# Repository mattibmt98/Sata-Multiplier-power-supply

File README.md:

# 5-Bay SATA Drive Power Supply

A 5-channel 12V/5V power board for a SATA port-multiplier drive cage, with
**passive analog staggered spin-up** so five drives never draw their inrush at
the same moment.

**Two 12V DC bricks in** (one barrel jack for bays 1–3, one for bays 4–5), five
12V+5V outputs out. No MCU, no hot-swap: each half powers up and down as a unit.

| | |
|---|---|
| Status | Schematic complete and verified · PCB routed, JLCPCB 2-layer rules |
| Board | 64.9 × 78.8 mm, single-sided placement, 118 parts |
| ERC / DRC | 0 errors, 0 unconnected, 0 schematic-parity issues (93 `connection_width` warnings, 86 of them inherited from v3) |
| BOM | `kicad/digikey_bom.csv`, fully sourced |
| Tool | KiCad 9 — open `kicad/sata_psu.kicad_pro` |

Tag [`v1.0`](../../releases/tag/v1.0) is the earlier single-buck board: 56 parts,
64.2 × 53.3 mm, same switch topology.

## What it does

- **Input, ×2:** barrel jack → 8A cartridge fuse → PMOS reverse-polarity guard →
  1000µF bulk, with a 12V indicator LED tapped *after* the guard so it also
  proves the guard is conducting. `J8` feeds `12V_A` (bays 1–3), `J9` feeds
  `12V_B` (bays 4–5). See "Two inputs" below.
- **Per channel (×5):** high-side P-channel MOSFET on the 12V feed, gate driven
  by an RC network so each channel turns on ~1.5–2s after the previous one and
  ramps softly instead of slamming in; 8.2V zener gate clamp; PPTC polyfuse;
  local bulk + HF decoupling; 4-pin header (12V / GND / GND / 5V) out to a SATA
  pigtail; a 5V indicator LED at the connector.
- **No 3.3V pin anywhere**, by construction — this sidesteps the SATA PWDIS
  failure mode entirely.

## Two inputs, two separate 12V rails

A fully populated cage pulls more than one PJ-063AH should carry — the jack is
an 8A contact and the single-input board fused it at 10A. So the load is
**split**, not paralleled:

```
J8 -> F8 -> Q8 -> 12V_A -> bays 1, 2, 3     worst case ~4.4A
J9 -> F9 -> Q9 -> 12V_B -> bays 4, 5        worst case ~3.4A
```

- The two rails are **never joined**; only ground is common. Two bricks in
  parallel do not share current, and an unplugged one would be back-fed.
- A 5–6A brick per jack is enough. Each half runs on its own: with only `J8`
  plugged, bays 1–3 work and 4–5 are simply off.
- With one to three drives, use bays 1–3 and a single brick on `J8`.
- The split follows the default 5V grouping (U2 → 1–3, U4 → 4–5). A 5V group
  that straddled the two inputs would feed 5V to a drive whose 12V is
  unplugged, so `verify.py` check 5 now refuses it (`DOMAINS` in `gen_sch.py`).

## The 5V rail is configurable, not fixed

Every port has its own local 5V node and its own buck footprint. Adjacent nodes
are joined by 0Ω links. **How a port gets its 5V is a populate choice, not a
layout one** — there is no board variant either way:

```
        U1        U2        U3        U4        U5      <- buck sites
       5V_1 -R61- 5V_2 -R62- 5V_3 -R63- 5V_4 -R64- 5V_5
```

Two tuples at the top of `gen_sch.py` are the whole configuration:

```python
# port:    1      2      3      4      5
BUCKS = (False, True,  False, True,  False)
LINKS = (True,  True,  False, True)        # R61..R64, between port n and n+1
```

The default is the economy build — U2 feeds ports 1–3, U4 feeds 4–5. All-True
`BUCKS` with all-False `LINKS` gives one independent buck per port.

**`R63` open is not decoration.** Fitting it with both U2 and U4 populated
parallels two regulators, and two bucks with slightly different setpoints do not
share load — the higher one takes everything and goes into current limit. That
build draws fine, exports a valid netlist and passes ERC, so `verify.py` check 5
is the only thing that catches it.

This is also what fixed v1's largest problem: one 3A TPS563200 was under-rated
against a five-bay 5V rail. Capping a buck at three ports makes its worst case
2.1A, and the same part is correctly sized.

## The schematic is generated, not drawn

Every coordinate, value and part number lives in Python. Do not hand-edit
the `.kicad_sch` sheets under `kicad/` — they are overwritten.

```bash
py sata_psu.py     # independent SKiDL reference netlist
py gen_sch.py      # build symbols + draw all 7 sheets
py verify.py       # the five checks below
```

**Do not run `gen_pcb.py` any more.** It produces an *unrouted* placement and
predates the routed board; `kicad/sata_psu.kicad_pcb` is now edited in KiCad
(or with pcbnew scripts) and is the source of truth for the layout.

`verify.py` cross-checks the drawn schematic against a *separately written*
SKiDL description of the same circuit, so a wire that only looks like it lands
on a pin gets caught. It runs five checks — ERC, symbol overlap, netlist
equivalence, symbol-pin-vs-pad, and the rail populate rules — each of which
exists because it catches something the others cannot see.

Details, and a list of KiCad file-format gotchas that cost real debugging time,
are in [HANDOFF.md](HANDOFF.md).

## Documents

- [`5bay_sata_psu_project.md`](5bay_sata_psu_project.md) — design intent: why
  staggered sequencing, power budget, block diagram, test plan.
- [`HANDOFF.md`](HANDOFF.md) — implementation: build pipeline, design decisions,
  placement rationale, BOM, and what changed in v2.

## Known open issues

1. Ceramic DC-bias derating will shorten the stagger versus the design table —
   the timing caps want bench tuning, or C0G/film for repeatability.
2. Linear-region SOA during the RC ramp is unverified against the real inrush.
3. The two inputs are staggered independently: bay 1 (domain A) and bay 4
   (domain B) each start their own RC ramp when their own brick is plugged in.
4. The 8A fuse cartridge's DigiKey number (`F2396-ND`) came from a web search
   of the listing, not from the cart — confirm it when ordering.

## Note on `libs/digikey/`

The vendored DigiKey KiCad library is not tracked here (12 MB, and unused — the
regulators moved to KiCad's own `Package_TO_SOT_SMD:SOT-23-6`).
`kicad/fp-lib-table` still carries the entry, so KiCad may warn about a missing
library on first open; either ignore it, drop the row, or restore the clone:

```bash
git clone --depth 1 https://github.com/Digi-Key/digikey-kicad-library libs/digikey
```

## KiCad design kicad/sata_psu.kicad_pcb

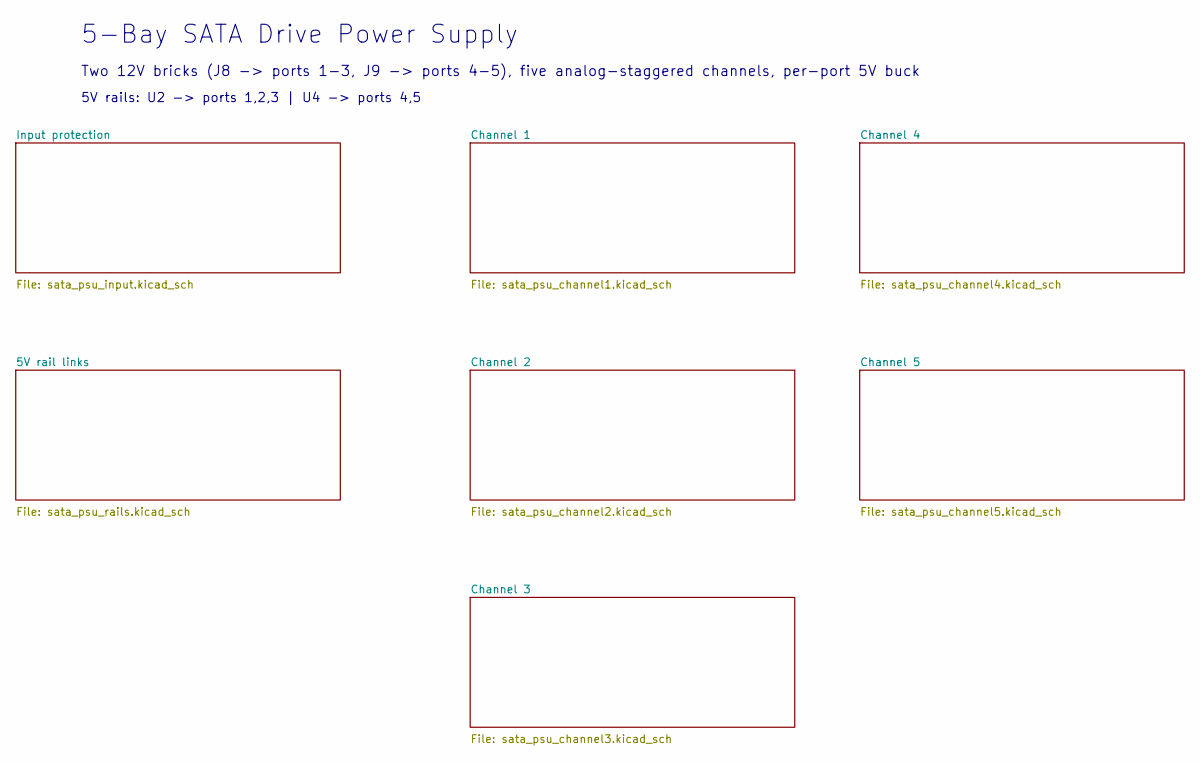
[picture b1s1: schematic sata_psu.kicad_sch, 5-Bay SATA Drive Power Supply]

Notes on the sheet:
5-Bay SATA Drive Power Supply
Two 12V bricks (J8 -> ports 1-3, J9 -> ports 4-5), five analog-staggered channels, per-port 5V buck
5V rails: U2 -> ports 1,2,3 | U4 -> ports 4,5

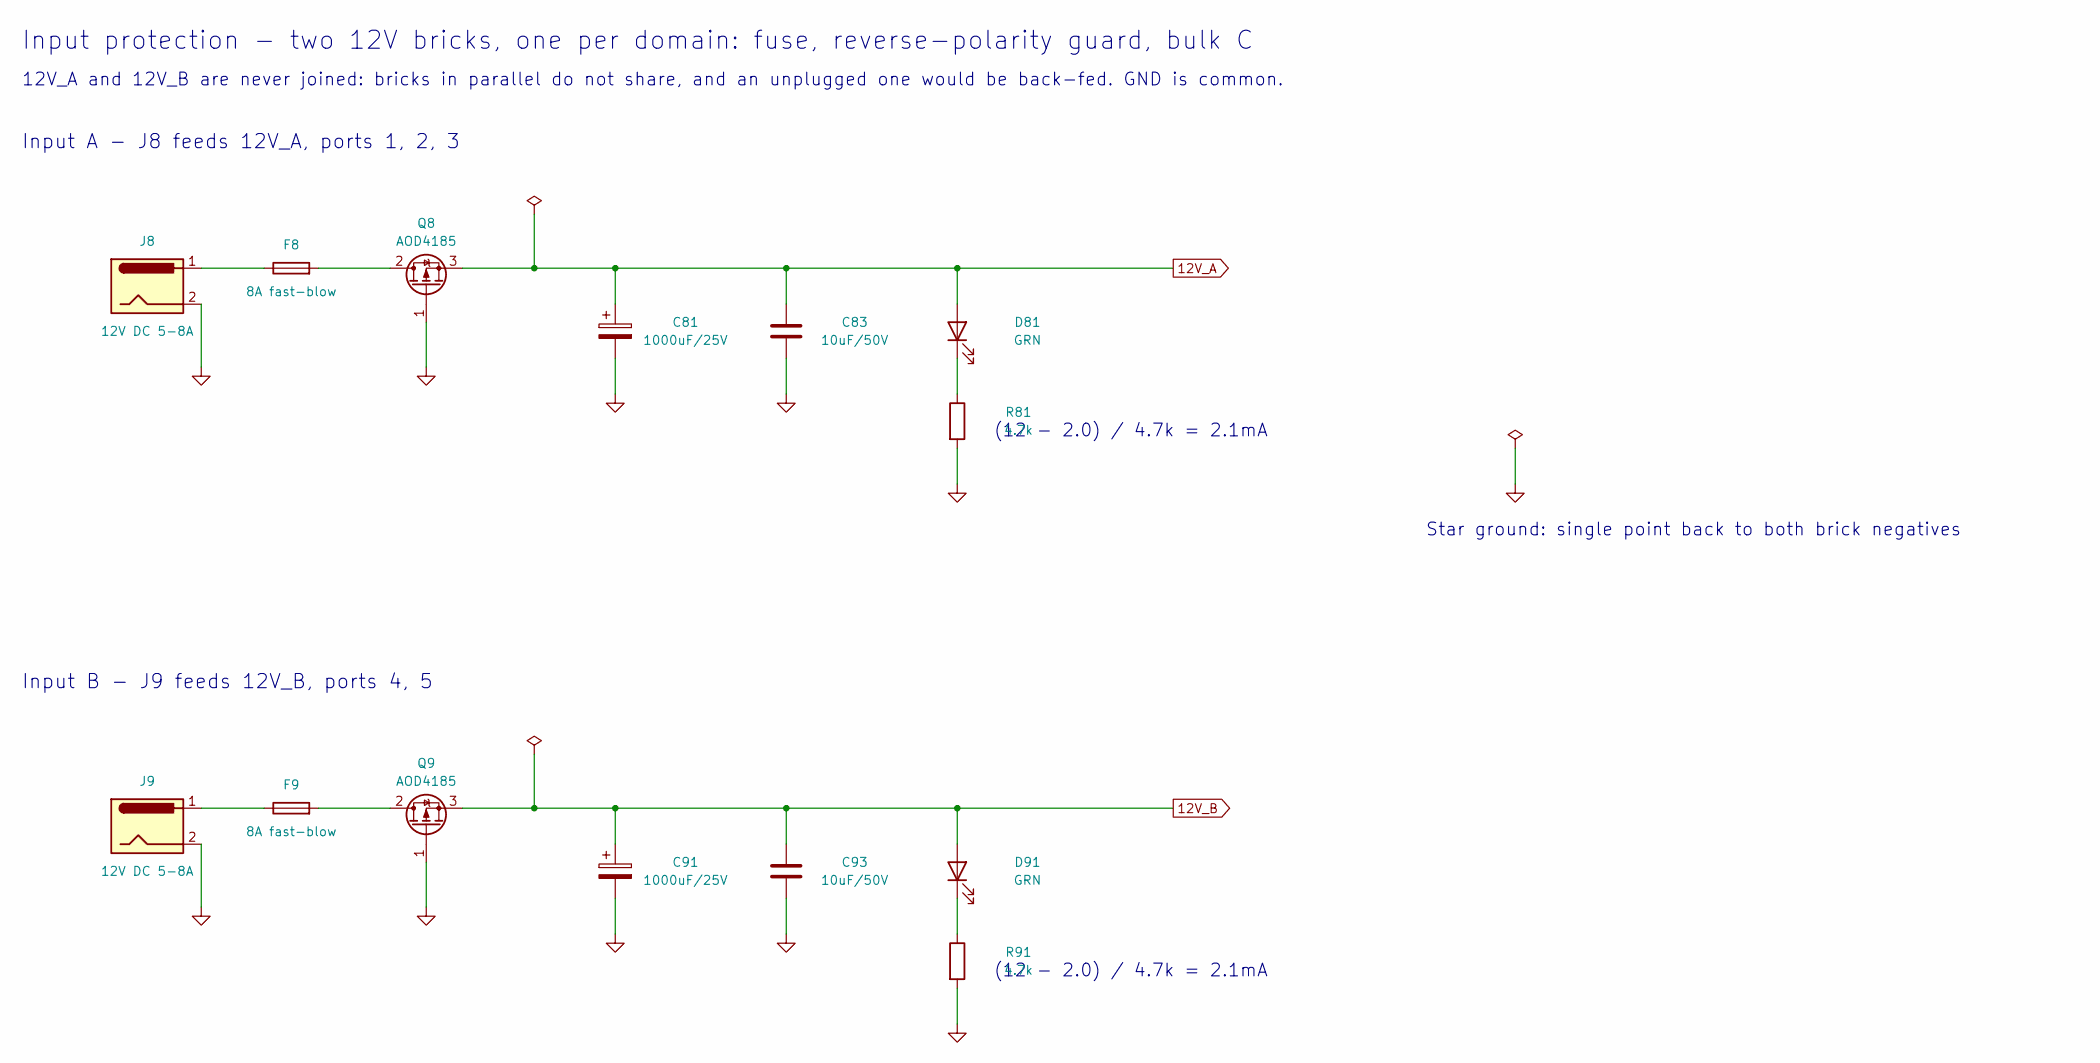
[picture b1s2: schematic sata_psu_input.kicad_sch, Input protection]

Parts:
C81, C91: 1000uF/25V; CP_Radial_D10.0mm_P5.00mm; MPN UVR1E102MPD; DigiKey 493-1065-ND
C83, C93: 10uF/50V; C_1206_3216Metric; MPN CL31A106KBHNNNE; DigiKey 1276-2876-1-ND
D81, D91: GRN; LED_0603_1608Metric
F8, F9: 8A fast-blow; Fuseholder_Clip-5x20mm_Bel_FC-203-22_Lateral_P17.80x5.00mm_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; MPN FC-203-22; DigiKey 507-1703-ND
J8, J9: 12V DC 5-8A; BarrelJack_CUI_PJ-063AH_Horizontal; MPN PJ-063AH; DigiKey CP-063AH-ND
Q8, Q9: AOD4185; TO-252-3_TabPin2; MPN AOD4185; DigiKey 785-1222-2-ND
R81, R91: 4.7k; R_0603_1608Metric

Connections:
12V_A: C81.1, C83.1, D81.2 (A), Q8.3 (S); also elsewhere on the board
12V_B: C91.1, C93.1, D91.2 (A), Q9.3 (S); also elsewhere on the board
GND: C81.2, C83.2, C91.2, C93.2, J8.2, J9.2, Q8.1 (G), Q9.1 (G), R81.2, R91.2; also elsewhere on the board
unnamed: D81.1 (K), R81.1
unnamed: D91.1 (K), R91.1
unnamed: F8.1, J8.1
unnamed: F9.1, J9.1
unnamed: F8.2, Q8.2 (D)
unnamed: F9.2, Q9.2 (D)

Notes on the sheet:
Input protection - two 12V bricks, one per domain: fuse, reverse-polarity guard, bulk C
12V_A and 12V_B are never joined: bricks in parallel do not share, and an unplugged one would be back-fed. GND is common.
Input A - J8 feeds 12V_A, ports 1, 2, 3
(12 - 2.0) / 4.7k = 2.1mA
Input B - J9 feeds 12V_B, ports 4, 5
Star ground: single point back to both brick negatives

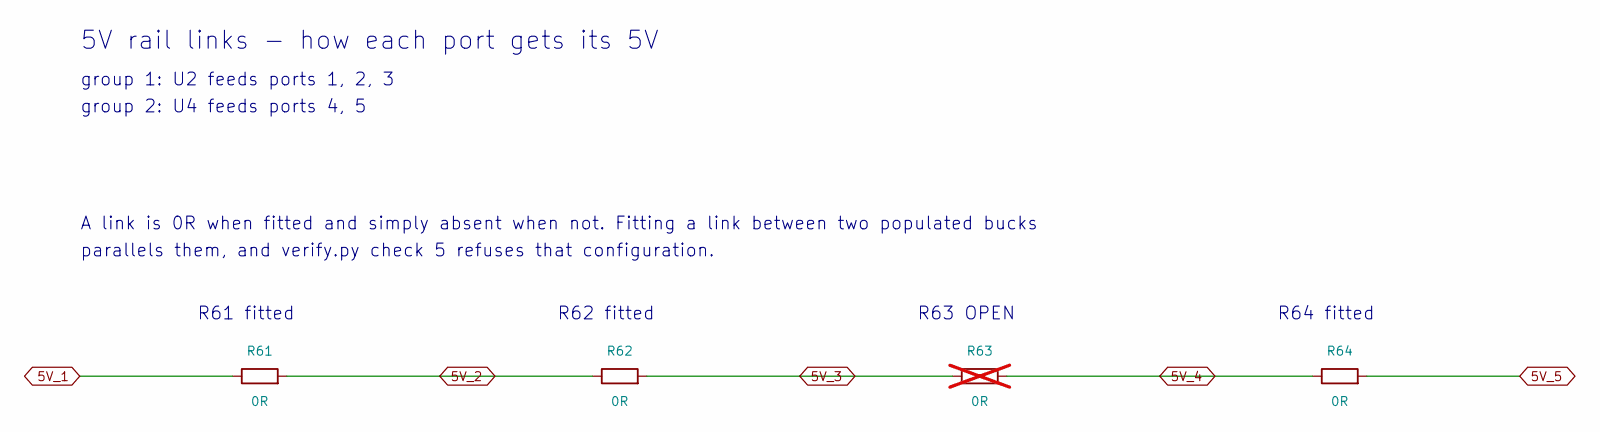
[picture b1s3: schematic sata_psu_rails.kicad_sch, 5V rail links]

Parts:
R61, R62, R64: 0R; R_1206_3216Metric
R63: 0R; R_1206_3216Metric; not fitted

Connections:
5V_1: R61.1; also elsewhere on the board
5V_2: R61.2, R62.1; also elsewhere on the board
5V_3: R62.2, R63.1; also elsewhere on the board
5V_4: R63.2, R64.1; also elsewhere on the board
5V_5: R64.2; also elsewhere on the board

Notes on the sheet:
5V rail links - how each port gets its 5V
group 1: U2 feeds ports 1, 2, 3
group 2: U4 feeds ports 4, 5
A link is 0R when fitted and simply absent when not. Fitting a link between two populated bucks
parallels them, and verify.py check 5 refuses that configuration.
R61 fitted
R62 fitted
R63 OPEN
R64 fitted

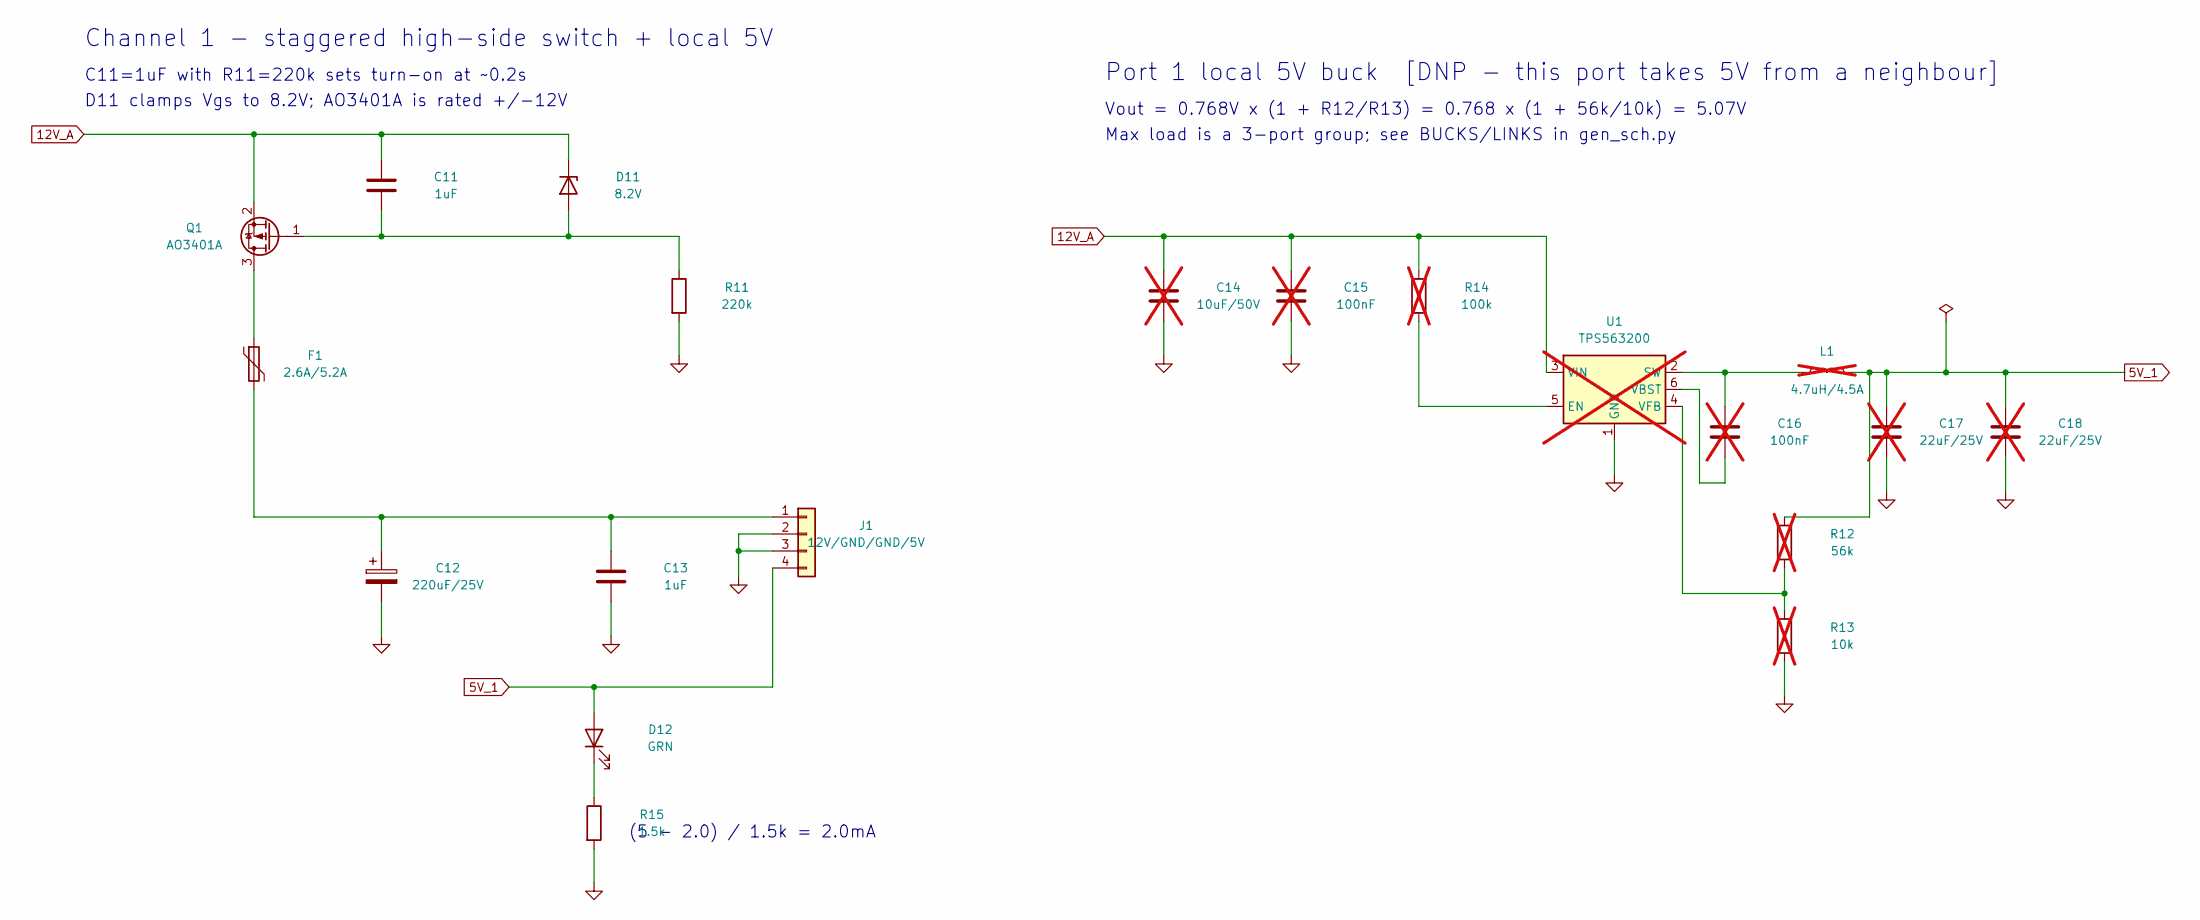
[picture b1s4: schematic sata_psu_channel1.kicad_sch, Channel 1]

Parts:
C11, C13: 1uF; C_0603_1608Metric; MPN CL10A105KB8NNNC; DigiKey 1276-1860-1-ND
C12: 220uF/25V; CP_Radial_D8.0mm_P3.50mm; MPN UVZ1E221MPD; DigiKey 493-1302-ND
C14: 10uF/50V; C_1206_3216Metric; MPN CL31A106KBHNNNE; DigiKey 1276-2876-1-ND; not fitted
C15, C16: 100nF; C_0603_1608Metric; MPN CL10B104KB8NNNC; DigiKey 1276-1000-1-ND; not fitted
C17, C18: 22uF/25V; C_1206_3216Metric; MPN CL31A226KAHNNNE; DigiKey 1276-3047-1-ND; not fitted
D11: 8.2V; D_SOD-123; MPN MMSZ5237B-7-F; DigiKey MMSZ5237B-FDICT-ND
D12: GRN; LED_0603_1608Metric
F1: 2.6A/5.2A; Fuse_1812_4532Metric; MPN 1812L260/16MR; DigiKey F10827CT-ND
J1: 12V/GND/GND/5V; PinHeader_1x04_P2.54mm_Vertical; MPN PRPC004SAAN-RC; DigiKey S1011EC-04-ND
L1: 4.7uH/4.5A; L_Bourns_SRN6045TA; MPN SRN6045TA-4R7M; DigiKey SRN6045TA-4R7MTR-ND; not fitted
Q1: AO3401A; SOT-23; MPN AO3401A; DigiKey 785-1001-1-ND
R11: 220k; R_0603_1608Metric; MPN RC0603FR-07220KL; DigiKey 311-220KHRCT-ND
R12: 56k; R_0603_1608Metric; MPN RC0603FR-0756KL; DigiKey 311-56KHRCT-ND; not fitted
R13: 10k; R_0603_1608Metric; MPN RC0603FR-0710KL; DigiKey 311-10.0KHRCT-ND; not fitted
R14: 100k; R_0603_1608Metric; MPN RC0603FR-07100KL; DigiKey 311-100KHRCT-ND; not fitted
R15: 1.5k; R_0603_1608Metric
U1: TPS563200; SOT-23-6; MPN TPS563200DDCR; DigiKey 296-43663-1-ND; not fitted

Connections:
5V_1: C17.1, C18.1, D12.2 (A), J1.4, L1.2, R12.1; also elsewhere on the board
12V_A: C11.1, C14.1, C15.1, D11.1 (K), Q1.2 (S), R14.1, U1.3 (VIN); also elsewhere on the board
GND: C12.2, C13.2, C14.2, C15.2, C17.2, C18.2, J1.2, J1.3, R11.2, R13.2, R15.2, U1.1 (GND); also elsewhere on the board
unnamed: C11.2, D11.2 (A), Q1.1 (G), R11.1
unnamed: D12.1 (K), R15.1
unnamed: C12.1, C13.1, F1.2, J1.1
unnamed: F1.1, Q1.3 (D)
unnamed: R14.2, U1.5 (EN)
unnamed: C16.1, L1.1, U1.2 (SW)
unnamed: C16.2, U1.6 (VBST)
unnamed: R12.2, R13.1, U1.4 (VFB)

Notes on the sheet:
Channel 1 - staggered high-side switch + local 5V
C11=1uF with R11=220k sets turn-on at ~0.2s
D11 clamps Vgs to 8.2V; AO3401A is rated +/-12V
(5 - 2.0) / 1.5k = 2.0mA
Port 1 local 5V buck [DNP - this port takes 5V from a neighbour]
Vout = 0.768V x (1 + R12/R13) = 0.768 x (1 + 56k/10k) = 5.07V
Max load is a 3-port group; see BUCKS/LINKS in gen_sch.py

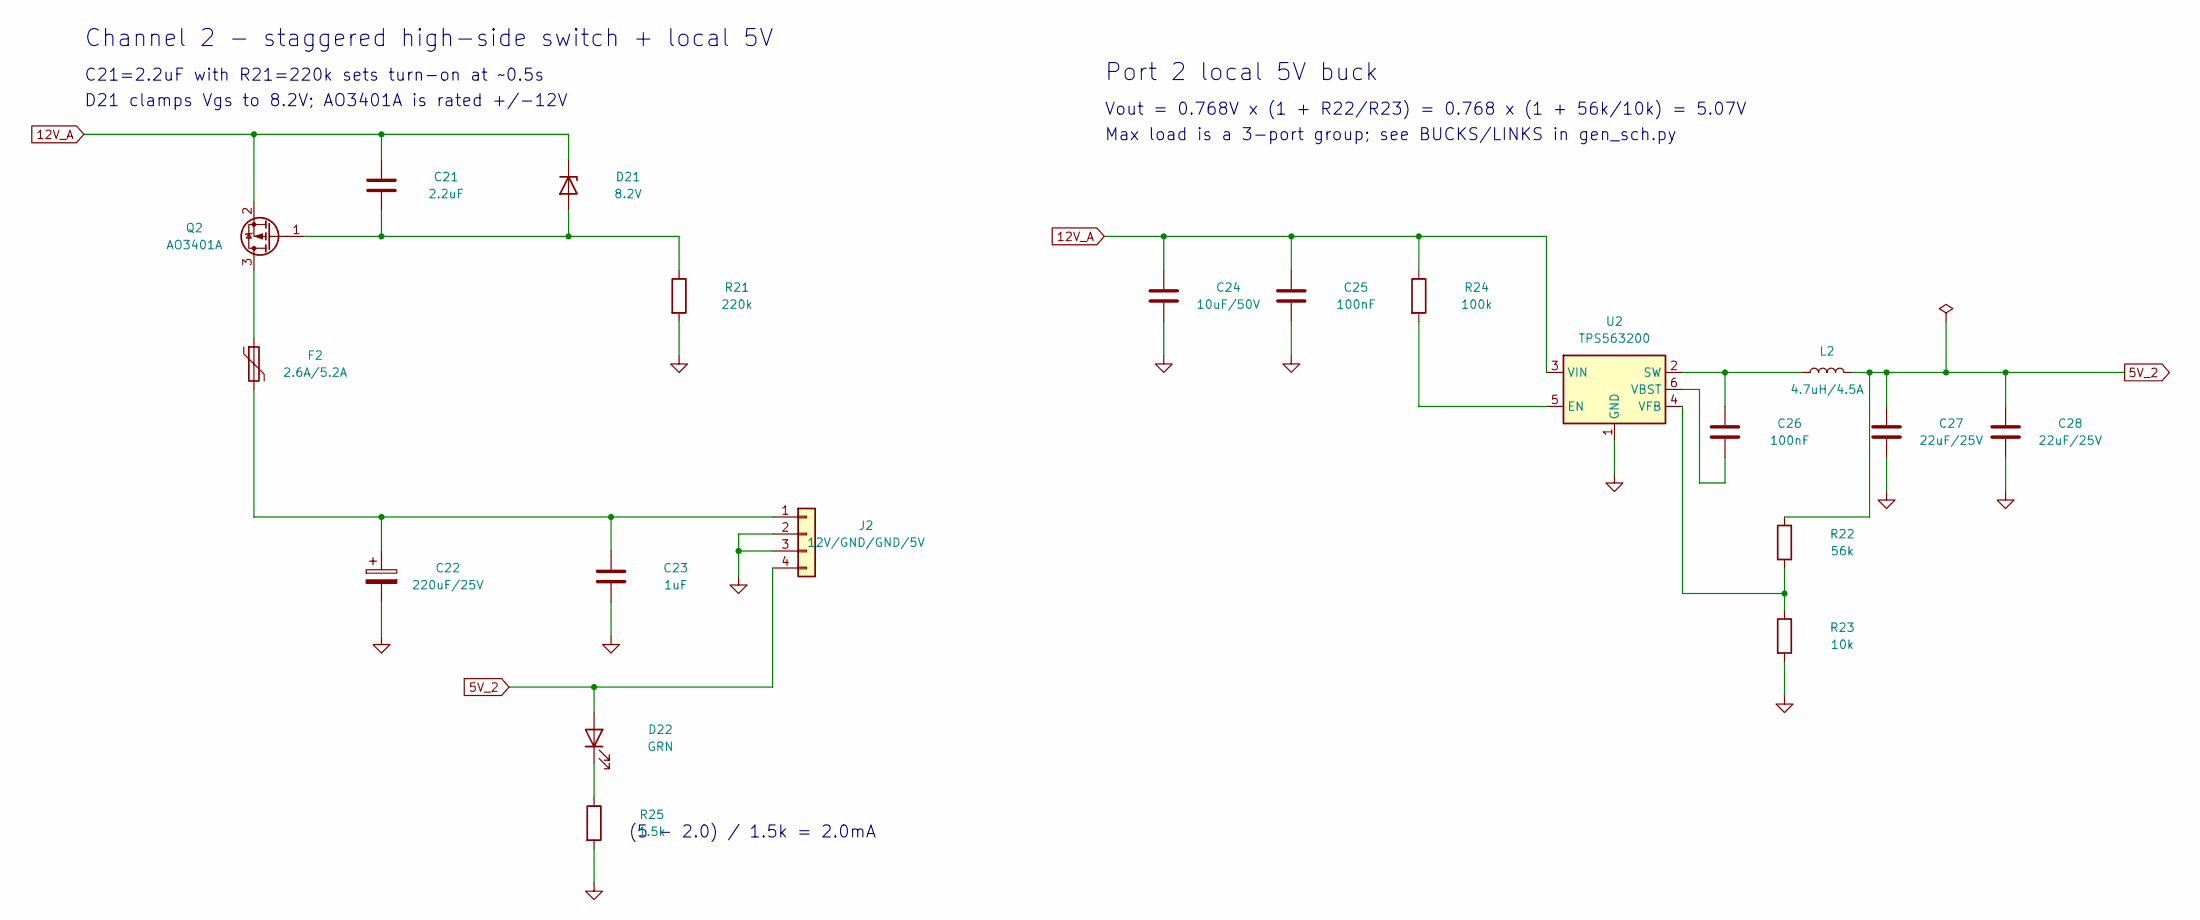
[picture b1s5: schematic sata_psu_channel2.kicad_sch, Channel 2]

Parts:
C21: 2.2uF; C_0603_1608Metric; MPN CL10A225KO8NNNC; DigiKey 1276-1040-1-ND
C22: 220uF/25V; CP_Radial_D8.0mm_P3.50mm; MPN UVZ1E221MPD; DigiKey 493-1302-ND
C23: 1uF; C_0603_1608Metric; MPN CL10A105KB8NNNC; DigiKey 1276-1860-1-ND
C24: 10uF/50V; C_1206_3216Metric; MPN CL31A106KBHNNNE; DigiKey 1276-2876-1-ND
C25, C26: 100nF; C_0603_1608Metric; MPN CL10B104KB8NNNC; DigiKey 1276-1000-1-ND
C27, C28: 22uF/25V; C_1206_3216Metric; MPN CL31A226KAHNNNE; DigiKey 1276-3047-1-ND
D21: 8.2V; D_SOD-123; MPN MMSZ5237B-7-F; DigiKey MMSZ5237B-FDICT-ND
D22: GRN; LED_0603_1608Metric
F2: 2.6A/5.2A; Fuse_1812_4532Metric; MPN 1812L260/16MR; DigiKey F10827CT-ND
J2: 12V/GND/GND/5V; PinHeader_1x04_P2.54mm_Vertical; MPN PRPC004SAAN-RC; DigiKey S1011EC-04-ND
L2: 4.7uH/4.5A; L_Bourns_SRN6045TA; MPN SRN6045TA-4R7M; DigiKey SRN6045TA-4R7MTR-ND
Q2: AO3401A; SOT-23; MPN AO3401A; DigiKey 785-1001-1-ND
R21: 220k; R_0603_1608Metric; MPN RC0603FR-07220KL; DigiKey 311-220KHRCT-ND
R22: 56k; R_0603_1608Metric; MPN RC0603FR-0756KL; DigiKey 311-56KHRCT-ND
R23: 10k; R_0603_1608Metric; MPN RC0603FR-0710KL; DigiKey 311-10.0KHRCT-ND
R24: 100k; R_0603_1608Metric; MPN RC0603FR-07100KL; DigiKey 311-100KHRCT-ND
R25: 1.5k; R_0603_1608Metric
U2: TPS563200; SOT-23-6; MPN TPS563200DDCR; DigiKey 296-43663-1-ND

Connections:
5V_2: C27.1, C28.1, D22.2 (A), J2.4, L2.2, R22.1; also elsewhere on the board
12V_A: C21.1, C24.1, C25.1, D21.1 (K), Q2.2 (S), R24.1, U2.3 (VIN); also elsewhere on the board
GND: C22.2, C23.2, C24.2, C25.2, C27.2, C28.2, J2.2, J2.3, R21.2, R23.2, R25.2, U2.1 (GND); also elsewhere on the board
unnamed: C21.2, D21.2 (A), Q2.1 (G), R21.1
unnamed: D22.1 (K), R25.1
unnamed: C22.1, C23.1, F2.2, J2.1
unnamed: F2.1, Q2.3 (D)
unnamed: R24.2, U2.5 (EN)
unnamed: C26.1, L2.1, U2.2 (SW)
unnamed: C26.2, U2.6 (VBST)
unnamed: R22.2, R23.1, U2.4 (VFB)

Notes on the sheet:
Channel 2 - staggered high-side switch + local 5V
C21=2.2uF with R21=220k sets turn-on at ~0.5s
D21 clamps Vgs to 8.2V; AO3401A is rated +/-12V
(5 - 2.0) / 1.5k = 2.0mA
Port 2 local 5V buck
Vout = 0.768V x (1 + R22/R23) = 0.768 x (1 + 56k/10k) = 5.07V
Max load is a 3-port group; see BUCKS/LINKS in gen_sch.py

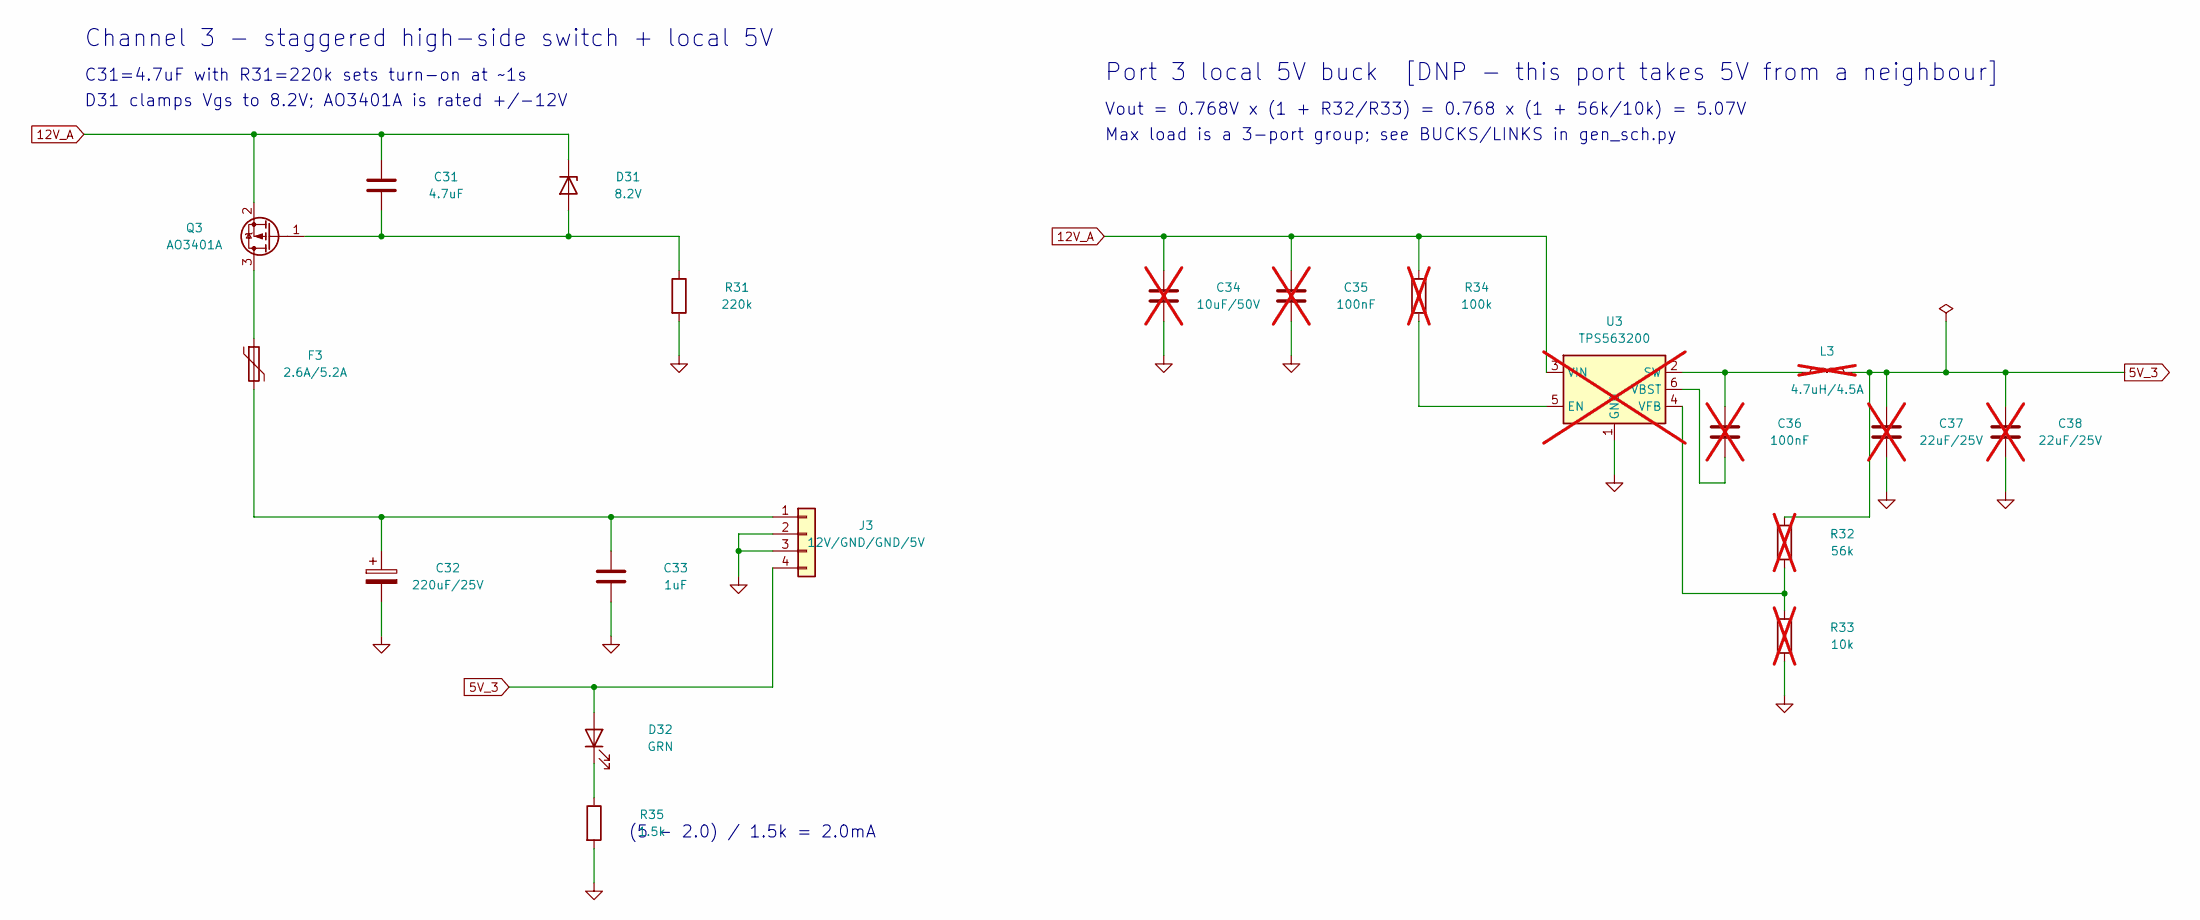
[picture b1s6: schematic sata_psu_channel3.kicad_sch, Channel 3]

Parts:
C31: 4.7uF; C_0603_1608Metric; MPN CL10A475KO8NNNC; DigiKey 1276-1784-1-ND
C32: 220uF/25V; CP_Radial_D8.0mm_P3.50mm; MPN UVZ1E221MPD; DigiKey 493-1302-ND
C33: 1uF; C_0603_1608Metric; MPN CL10A105KB8NNNC; DigiKey 1276-1860-1-ND
C34: 10uF/50V; C_1206_3216Metric; MPN CL31A106KBHNNNE; DigiKey 1276-2876-1-ND; not fitted
C35, C36: 100nF; C_0603_1608Metric; MPN CL10B104KB8NNNC; DigiKey 1276-1000-1-ND; not fitted
C37, C38: 22uF/25V; C_1206_3216Metric; MPN CL31A226KAHNNNE; DigiKey 1276-3047-1-ND; not fitted
D31: 8.2V; D_SOD-123; MPN MMSZ5237B-7-F; DigiKey MMSZ5237B-FDICT-ND
D32: GRN; LED_0603_1608Metric
F3: 2.6A/5.2A; Fuse_1812_4532Metric; MPN 1812L260/16MR; DigiKey F10827CT-ND
J3: 12V/GND/GND/5V; PinHeader_1x04_P2.54mm_Vertical; MPN PRPC004SAAN-RC; DigiKey S1011EC-04-ND
L3: 4.7uH/4.5A; L_Bourns_SRN6045TA; MPN SRN6045TA-4R7M; DigiKey SRN6045TA-4R7MTR-ND; not fitted
Q3: AO3401A; SOT-23; MPN AO3401A; DigiKey 785-1001-1-ND
R31: 220k; R_0603_1608Metric; MPN RC0603FR-07220KL; DigiKey 311-220KHRCT-ND
R32: 56k; R_0603_1608Metric; MPN RC0603FR-0756KL; DigiKey 311-56KHRCT-ND; not fitted
R33: 10k; R_0603_1608Metric; MPN RC0603FR-0710KL; DigiKey 311-10.0KHRCT-ND; not fitted
R34: 100k; R_0603_1608Metric; MPN RC0603FR-07100KL; DigiKey 311-100KHRCT-ND; not fitted
R35: 1.5k; R_0603_1608Metric
U3: TPS563200; SOT-23-6; MPN TPS563200DDCR; DigiKey 296-43663-1-ND; not fitted

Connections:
5V_3: C37.1, C38.1, D32.2 (A), J3.4, L3.2, R32.1; also elsewhere on the board
12V_A: C31.1, C34.1, C35.1, D31.1 (K), Q3.2 (S), R34.1, U3.3 (VIN); also elsewhere on the board
GND: C32.2, C33.2, C34.2, C35.2, C37.2, C38.2, J3.2, J3.3, R31.2, R33.2, R35.2, U3.1 (GND); also elsewhere on the board
unnamed: C31.2, D31.2 (A), Q3.1 (G), R31.1
unnamed: D32.1 (K), R35.1
unnamed: C32.1, C33.1, F3.2, J3.1
unnamed: F3.1, Q3.3 (D)
unnamed: R34.2, U3.5 (EN)
unnamed: C36.1, L3.1, U3.2 (SW)
unnamed: C36.2, U3.6 (VBST)
unnamed: R32.2, R33.1, U3.4 (VFB)

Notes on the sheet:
Channel 3 - staggered high-side switch + local 5V
C31=4.7uF with R31=220k sets turn-on at ~1s
D31 clamps Vgs to 8.2V; AO3401A is rated +/-12V
(5 - 2.0) / 1.5k = 2.0mA
Port 3 local 5V buck [DNP - this port takes 5V from a neighbour]
Vout = 0.768V x (1 + R32/R33) = 0.768 x (1 + 56k/10k) = 5.07V
Max load is a 3-port group; see BUCKS/LINKS in gen_sch.py

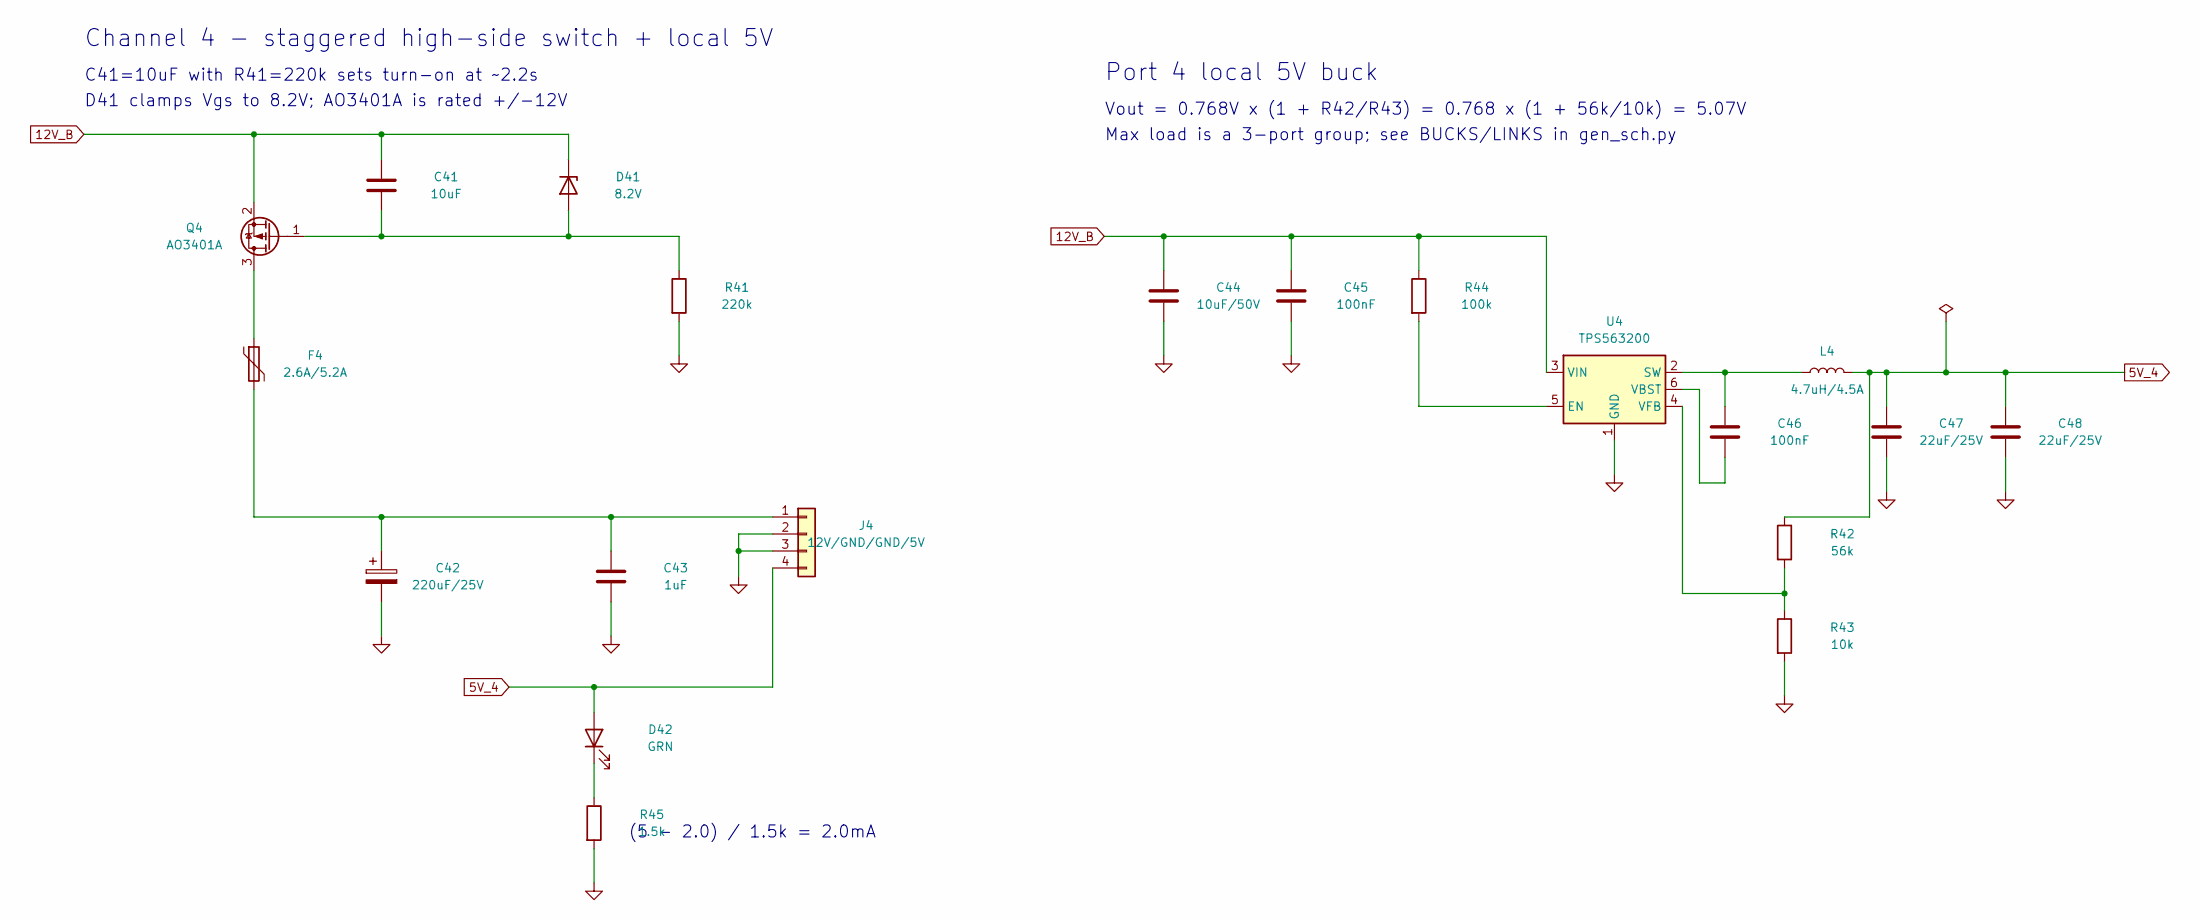
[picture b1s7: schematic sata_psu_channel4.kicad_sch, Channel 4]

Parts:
C41: 10uF; C_1206_3216Metric; MPN CL31A106KBHNNNE; DigiKey 1276-2876-1-ND
C42: 220uF/25V; CP_Radial_D8.0mm_P3.50mm; MPN UVZ1E221MPD; DigiKey 493-1302-ND
C43: 1uF; C_0603_1608Metric; MPN CL10A105KB8NNNC; DigiKey 1276-1860-1-ND
C44: 10uF/50V; C_1206_3216Metric; MPN CL31A106KBHNNNE; DigiKey 1276-2876-1-ND
C45, C46: 100nF; C_0603_1608Metric; MPN CL10B104KB8NNNC; DigiKey 1276-1000-1-ND
C47, C48: 22uF/25V; C_1206_3216Metric; MPN CL31A226KAHNNNE; DigiKey 1276-3047-1-ND
D41: 8.2V; D_SOD-123; MPN MMSZ5237B-7-F; DigiKey MMSZ5237B-FDICT-ND
D42: GRN; LED_0603_1608Metric
F4: 2.6A/5.2A; Fuse_1812_4532Metric; MPN 1812L260/16MR; DigiKey F10827CT-ND
J4: 12V/GND/GND/5V; PinHeader_1x04_P2.54mm_Vertical; MPN PRPC004SAAN-RC; DigiKey S1011EC-04-ND
L4: 4.7uH/4.5A; L_Bourns_SRN6045TA; MPN SRN6045TA-4R7M; DigiKey SRN6045TA-4R7MTR-ND
Q4: AO3401A; SOT-23; MPN AO3401A; DigiKey 785-1001-1-ND
R41: 220k; R_0603_1608Metric; MPN RC0603FR-07220KL; DigiKey 311-220KHRCT-ND
R42: 56k; R_0603_1608Metric; MPN RC0603FR-0756KL; DigiKey 311-56KHRCT-ND
R43: 10k; R_0603_1608Metric; MPN RC0603FR-0710KL; DigiKey 311-10.0KHRCT-ND
R44: 100k; R_0603_1608Metric; MPN RC0603FR-07100KL; DigiKey 311-100KHRCT-ND
R45: 1.5k; R_0603_1608Metric
U4: TPS563200; SOT-23-6; MPN TPS563200DDCR; DigiKey 296-43663-1-ND

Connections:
5V_4: C47.1, C48.1, D42.2 (A), J4.4, L4.2, R42.1; also elsewhere on the board
12V_B: C41.1, C44.1, C45.1, D41.1 (K), Q4.2 (S), R44.1, U4.3 (VIN); also elsewhere on the board
GND: C42.2, C43.2, C44.2, C45.2, C47.2, C48.2, J4.2, J4.3, R41.2, R43.2, R45.2, U4.1 (GND); also elsewhere on the board
unnamed: C41.2, D41.2 (A), Q4.1 (G), R41.1
unnamed: D42.1 (K), R45.1
unnamed: C42.1, C43.1, F4.2, J4.1
unnamed: F4.1, Q4.3 (D)
unnamed: R44.2, U4.5 (EN)
unnamed: C46.1, L4.1, U4.2 (SW)
unnamed: C46.2, U4.6 (VBST)
unnamed: R42.2, R43.1, U4.4 (VFB)

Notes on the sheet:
Channel 4 - staggered high-side switch + local 5V
C41=10uF with R41=220k sets turn-on at ~2.2s
D41 clamps Vgs to 8.2V; AO3401A is rated +/-12V
(5 - 2.0) / 1.5k = 2.0mA
Port 4 local 5V buck
Vout = 0.768V x (1 + R42/R43) = 0.768 x (1 + 56k/10k) = 5.07V
Max load is a 3-port group; see BUCKS/LINKS in gen_sch.py
